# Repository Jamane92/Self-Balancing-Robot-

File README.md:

# Self-Balancing-Robot-

--FRANCAIS--

Ce projet à été réalisé individuellement en parallèle de mes études, reprend un projet que nous avions réalisé en ING1 à l'ECE Paris. Mais cette fois, au lieu de tout avoir déjà donné et pensé dans un kit, je me suis lancé le défi de tout faire moi même, de A à Z, de la 3D à la création du PCB, au codage du PID. Voici le résultat final : 

--ENGLISH

I carried out this project independently alongside my studies, revisiting a project we had originally completed during our first year of engineering school (ING1) at ECE Paris. This time, however, instead of using a kit where everything was pre-designed and provided, I challenged myself to build the entire thing from scratch—from 3D modeling and PCB design to programming the PID controller. Here is the final result : 

--FRANCAIS--
Si souhaité, ce robort peut-être transformé en robot télécommandé, il suffit simplement de créer un serveur web sur l'EPS32 et d'y ajouter une modification de la consigne d'angle, ou de set un pitch/roll cible. 

Les difficultés rencontrés ont été sur le codage du PID, le fait que le buck-down choisi, le Mini360, ne donnait probablement pas suffisament de courant, bridant le couple et compliquant ainsi le codage du PID, j'ai également eu quelque problèmes avec le placement de mon MPU-6050, qui est un module bassse qualité, qui m'a beaucoup ralenti, en effet, pas malin d'acheter le coeur du projet à 3e sur Aliexpress au lieu de 15e chez le constructeur. Egalement celui-ci à été mal placé, ce que j'ai corrigé avec le point de col sur le coté pour le mettre à l'horizontal et non à la verticale ccomme il l'était. Aussi, j'ai "verser du cuivre" en GND sous l'antenne, ce qui n'est pas bon pour l'intégrité du signal radio et réduisait ainsi mes performances WIFI. C'est néanmoins un premier projet validé, qui me donne confiance pour plonger plus en détail dans le monde des PCB et de la conception hardware. 

--ENGLISH--
If desired, this robot can be converted into a remote-controlled unit; this simply requires setting up a web server on the ESP32 and adding a way to modify the angle setpoint or define a target pitch/roll.

I encountered difficulties with the PID coding, partly because the chosen step-down converter (the Mini360) likely didn't supply enough current—limiting torque and complicating PID tuning. I also faced issues with the placement of the MPU-6050; it was a low-quality module that really slowed me down—in hindsight, buying the project's core component for €3 on AliExpress instead of €15 from the manufacturer wasn't the smartest move. Furthermore, its initial positioning was incorrect; I fixed this by mounting it horizontally (using a side-mounted glue point) rather than vertically as it had been before. Finally, I had "poured copper" (a ground plane) beneath the antenna, which compromised radio signal integrity and reduced Wi-Fi performance. It is, however, a first project successfully completed, giving me the confidence to delve deeper into the world of PCBs and hardware design.

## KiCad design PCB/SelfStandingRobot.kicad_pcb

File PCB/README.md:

--FRANCAIS-- 

Voici la section PCB du projet, j'y expose l'intégralité des documents nécessaires pour récupéerer le projet. Ce projet avait avant tout pour but de m'initier à la création de mon tout premier PCB, il n'utilise que des composants THT ou module complet que j'ai implémenté sur le PCB. Voici à quoi ressemble la 3D de mon PCB : 

--ENGLISH--

Here is the PCB section of the project; I have provided all the necessary documents to replicate it. The primary goal of this project was to learn how to design my very first PCB; it uses only through-hole (THT) components or complete modules that I mounted onto the board. Here is what the 3D view of my PCB looks like:

--FRANCAIS--

Et voici le routage, gardez à l'esprit que c'est mon tout premier PCB, avec que des composants THT, sans copper zone pour la puissance par exemple, sans plan de masse correct garantissant des EMI basses et une intégrité du signal, même si sur ce genre d'application, on est loin d'avoir ce genre de problème. L'important pour moi à ce moment là, c'était que ca marche, pour me donner la confiance d'aller sur des projets plus poussés.

--ENGLISH--

And here is the routing; keep in mind that this is my very first PCB, using only through-hole components, with no copper pour and no proper ground plane to ensure low EMI and signal integrity—though for this type of application, such issues are far from being a concern. The important thing for me at that point was for it to work, to give me the confidence to take on more advanced projects.

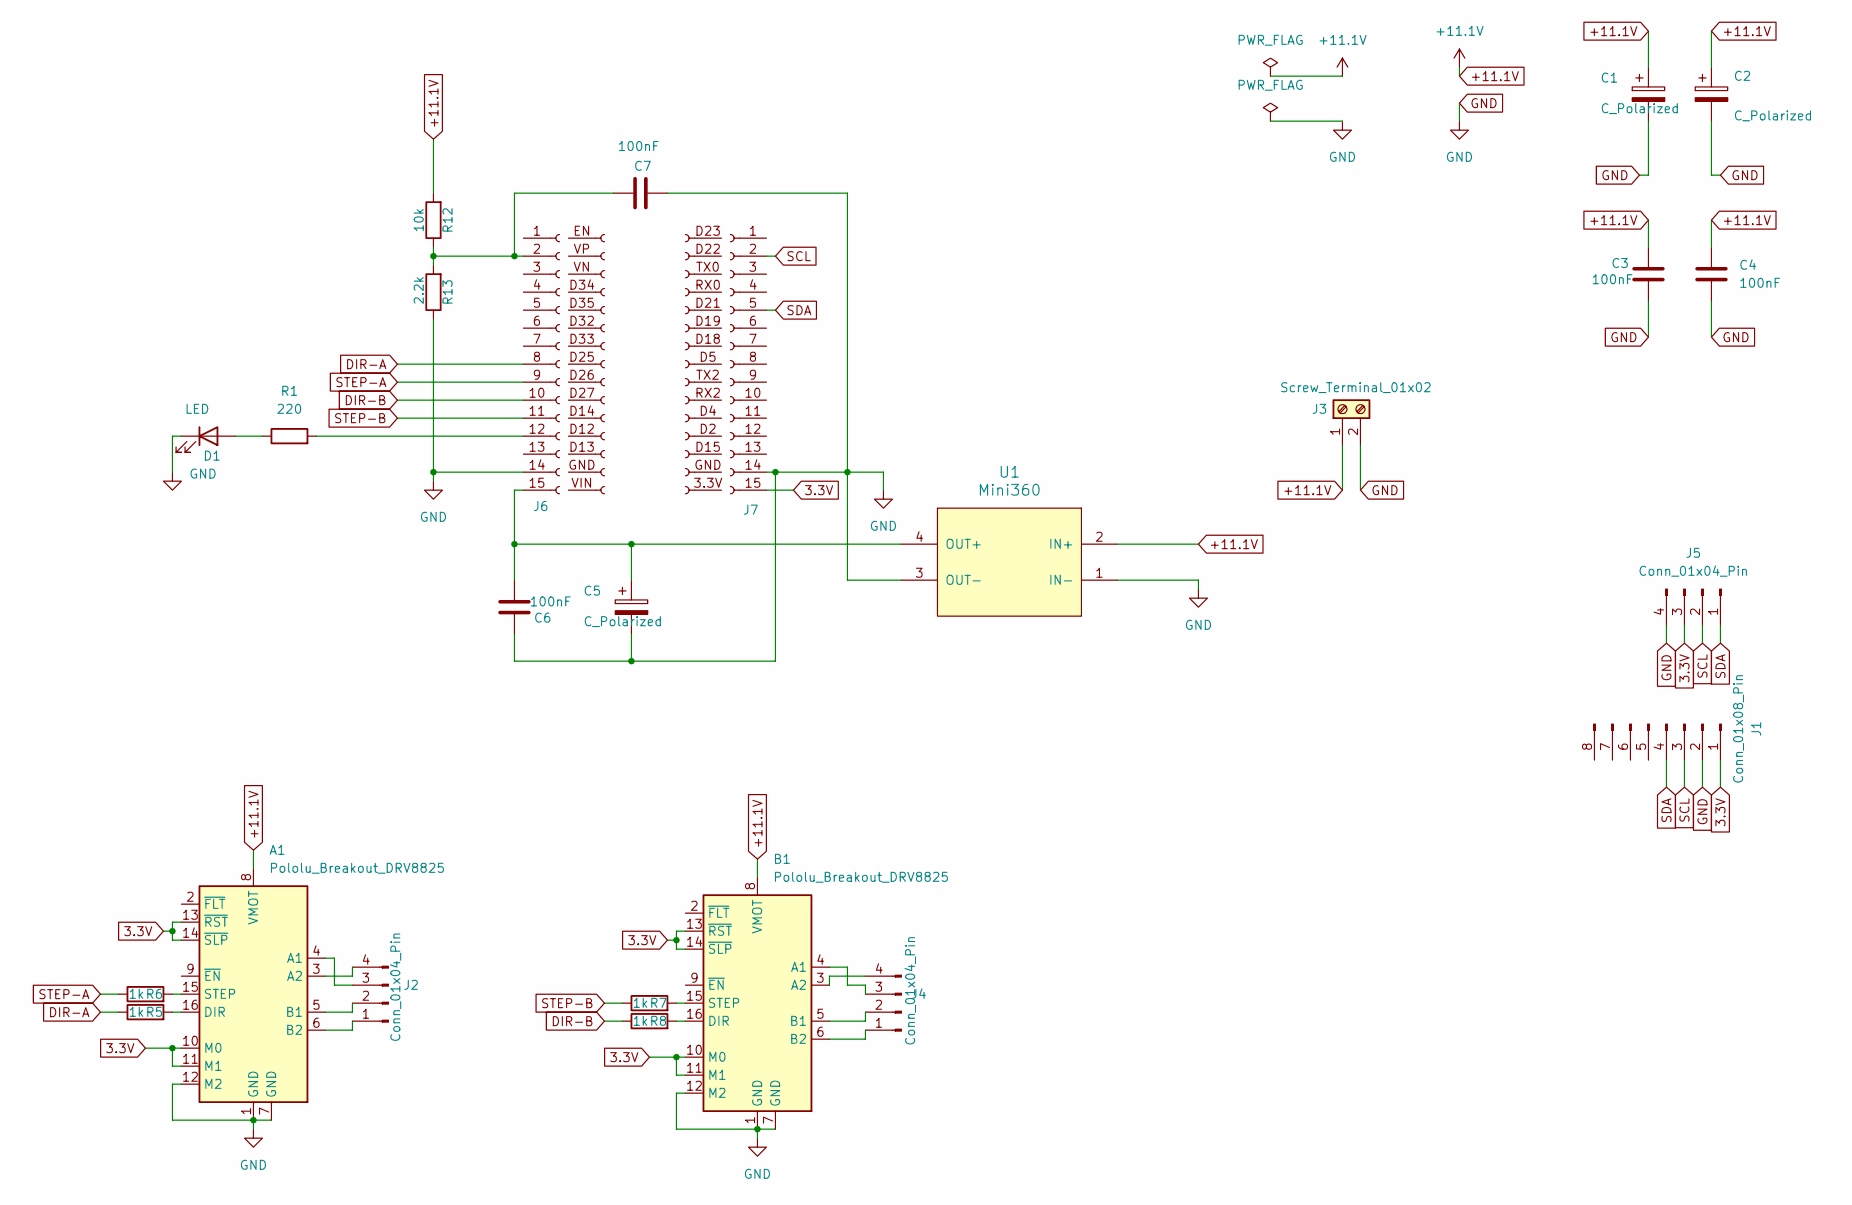
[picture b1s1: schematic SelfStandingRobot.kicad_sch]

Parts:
A1: Pololu_Breakout_DRV8825; Pololu_Breakout-16_15.2x20.3mm
B1: Pololu_Breakout_DRV8825; Pololu_Breakout-16_15.2x20.3mm
C1, C2, C5: C_Polarized; CP_Radial_D8.0mm_P5.00mm
C3, C4, C6, C7: 100nF; C_Disc_D3.0mm_W1.6mm_P2.50mm
D1: LED; LED_D5.0mm
J1: Conn_01x08_Pin; PinSocket_1x08_P2.54mm_Vertical
J2, J4, J5: Conn_01x04_Pin; PinHeader_1x04_P2.54mm_Vertical
J3: Screw_Terminal_01x02; TerminalBlock_Phoenix_MKDS-1,5-2-5.08_1x02_P5.08mm_Horizont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
J6, J7: Conn_01x15_Socket; PinSocket_1x15_P2.54mm_Vertical
J9, J10: Conn_01x15_Socket
R1: 220; R_Axial_DIN0207_L6.3mm_D2.5mm_P7.62mm_Horizontal
R5, R6, R7, R8: 1k; R_Axial_DIN0207_L6.3mm_D2.5mm_P7.62mm_Horizontal
R12: 10k; R_Axial_DIN0207_L6.3mm_D2.5mm_P7.62mm_Horizontal
R13: 2.2k; R_Axial_DIN0207_L6.3mm_D2.5mm_P7.62mm_Horizontal
U1: Mini360; Mini360_Step-Down

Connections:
3.3V: A1.10 (M0), A1.11 (M1), A1.13 (~RST), A1.14 (~SLP), B1.10 (M0), B1.11 (M1), B1.13 (~RST), B1.14 (~SLP), J1.1, J5.3, J7.15 (3.3V)
+11.1V: A1.8 (VMOT), B1.8 (VMOT), C1.1, C2.1, C3.1, C4.1, J3.1, R12.2, U1.2 (IN+)
DIR-A: J6.8 (D25), R5.1
DIR-B: J6.10 (D27), R8.1
GND: A1.1 (GND), A1.7 (GND), A1.12 (M2), B1.1 (GND), B1.7 (GND), B1.12 (M2), C1.2, C2.2, C3.2, C4.2, C5.2, C6.1, C7.1, D1.1 (K), J1.2, J3.2, J5.4, J6.14 (GND), J7.14 (GND), R13.1, U1.1 (IN-), U1.3 (OUT-)
unnamed: A1.4 (A1), J2.3
unnamed: A1.3 (A2), J2.4
unnamed: A1.5 (B1), J2.2
unnamed: A1.6 (B2), J2.1
unnamed: A1.16 (DIR), R5.2
unnamed: A1.15 (STEP), R6.2
unnamed: B1.4 (A1), J4.3
unnamed: B1.3 (A2), J4.4
unnamed: B1.5 (B1), J4.2
unnamed: B1.6 (B2), J4.1
unnamed: B1.16 (DIR), R8.2
unnamed: B1.15 (STEP), R7.2
unnamed: D1.2 (A), R1.1
unnamed: J6.12 (D12), R1.2
unnamed: C5.1, C6.2, J6.15 (VIN), U1.4 (OUT+)
unnamed: C7.2, J6.2 (VP), R12.1, R13.2
SCL: J1.3, J5.2, J7.2 (D22)
SDA: J1.4, J5.1, J7.5 (D21)
STEP-A: J6.9 (D26), R6.1
STEP-B: J6.11 (D14), R7.1

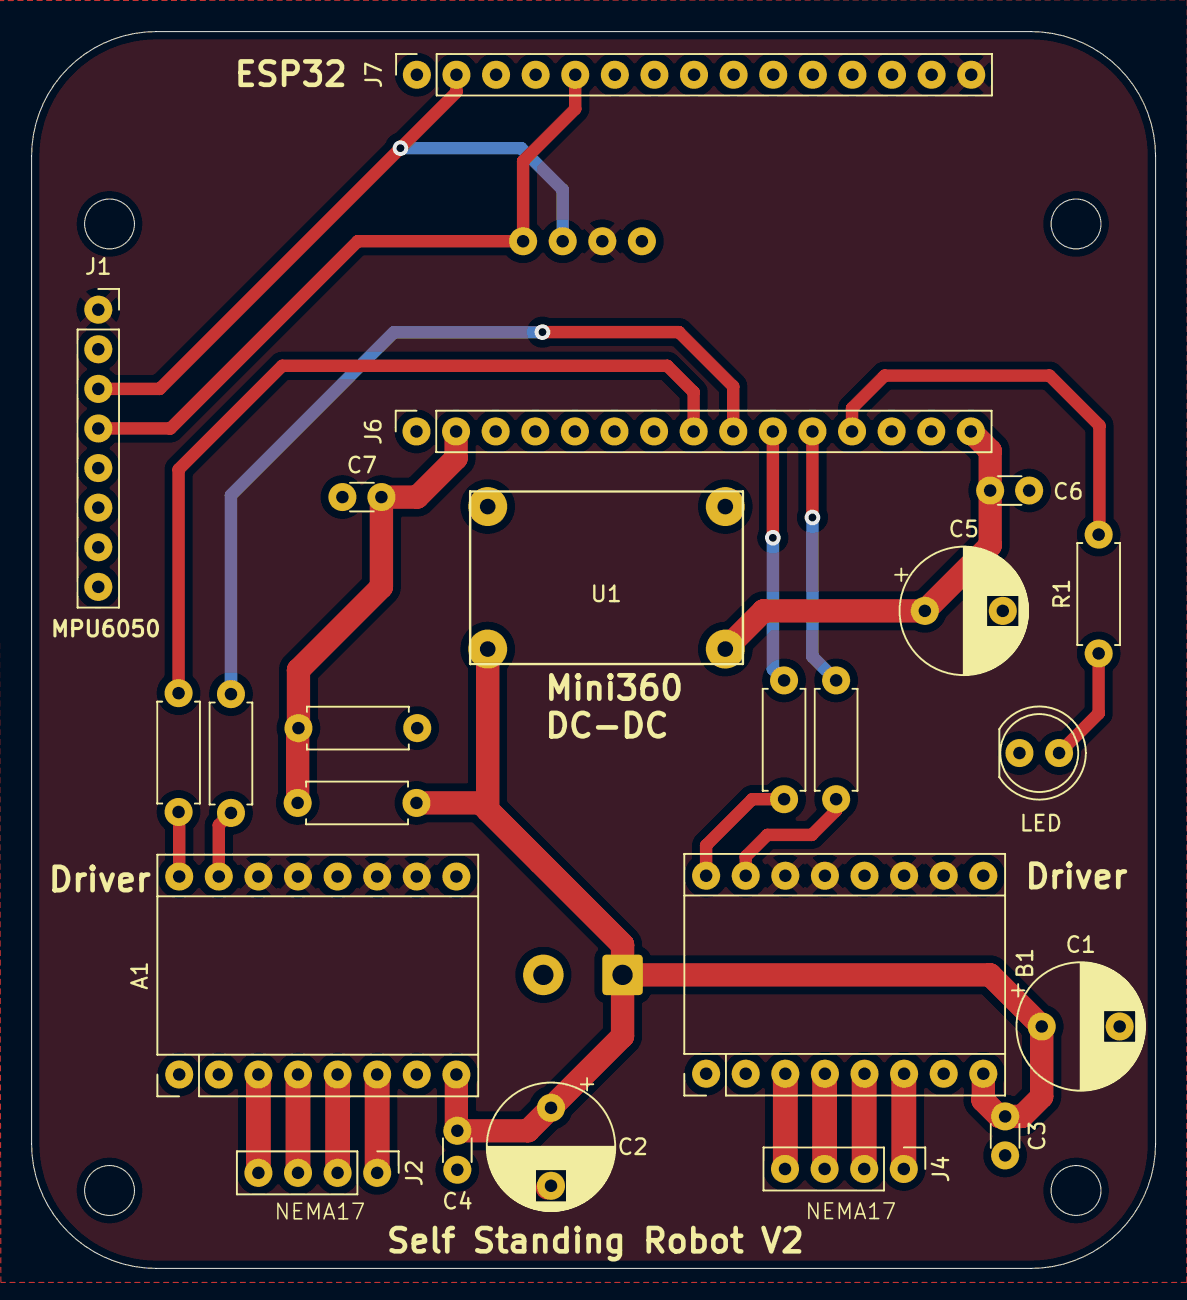
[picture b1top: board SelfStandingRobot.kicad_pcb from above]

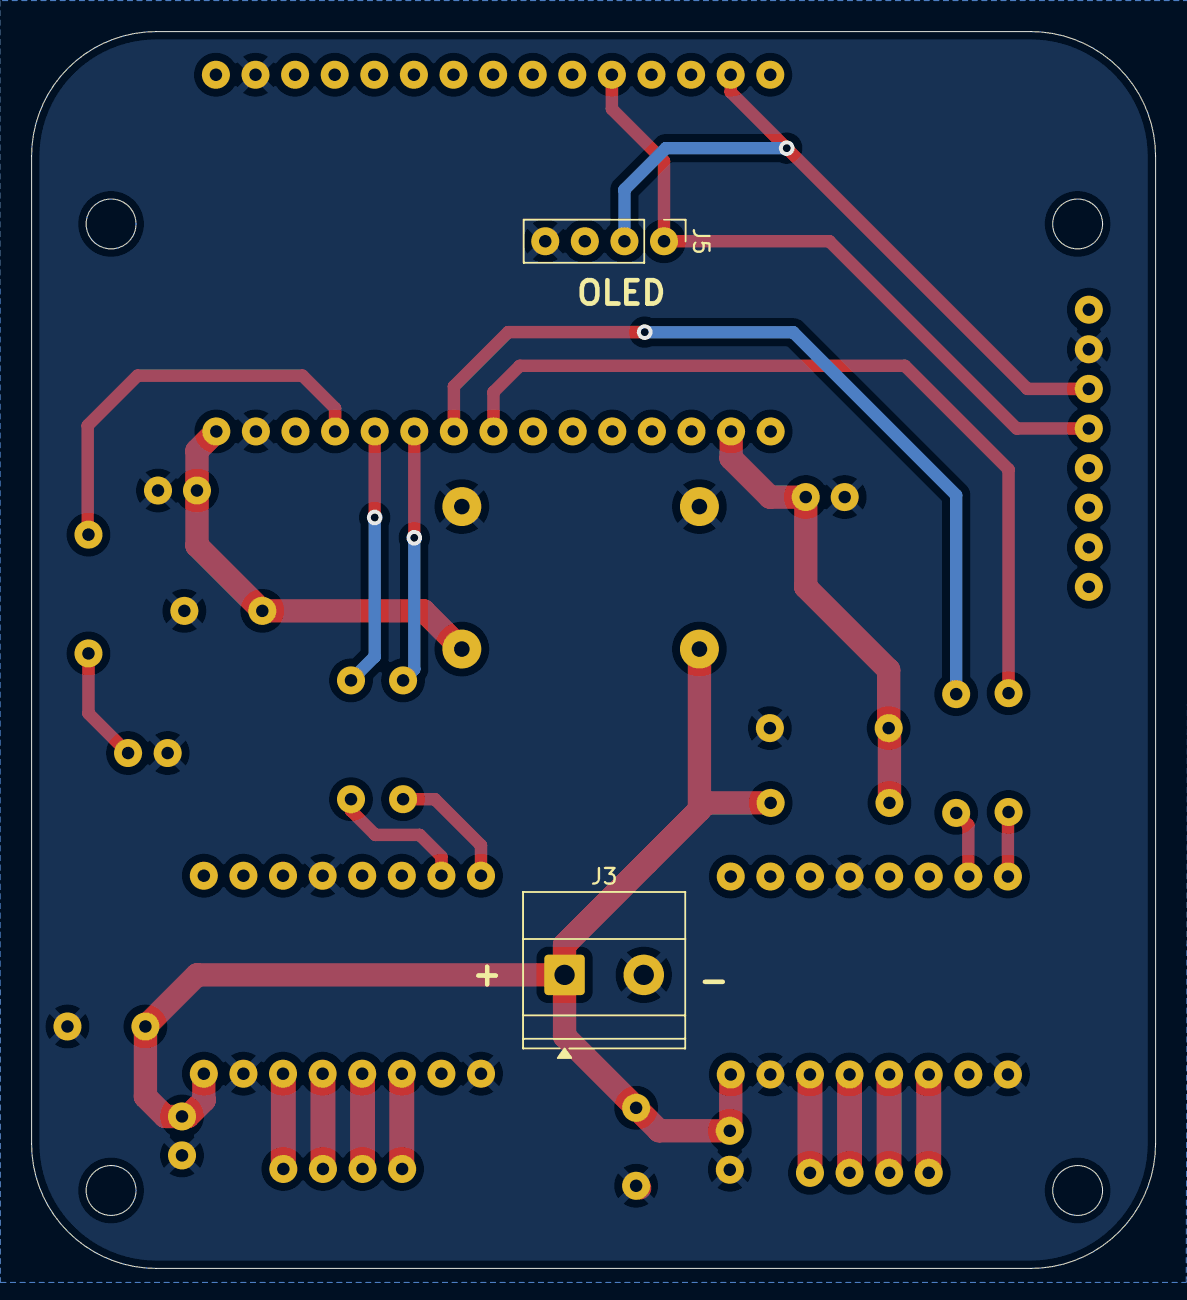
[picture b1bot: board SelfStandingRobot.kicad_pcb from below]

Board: 2 copper layers, 72.1 x 79.3 mm, 25 parts (2 on the bottom side), 25 nets.
